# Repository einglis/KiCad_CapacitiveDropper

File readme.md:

# Gate Light Capacitive Dropper

I bought some LED tape (https://www.amazon.co.uk/dp/B07KW4Q4R3) to make lights for my gateposts.

In stock trim, they're too bright, and they flicker in my peripheral vision, which is very annoying.

BigClive has a nice article about hacking LED bulbs here: https://bigclive.com/ledlmp.htm.  It applies equally well to these LED tapes.

Because I'm indecisive, I made three variants...

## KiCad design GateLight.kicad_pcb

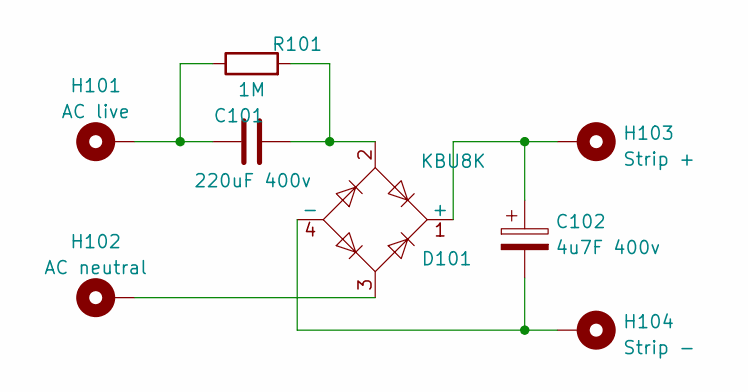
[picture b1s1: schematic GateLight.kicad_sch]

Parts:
C101: 220uF 400v; C_Rect_L16.5mm_W9.2mm_P15.00mm_MKT
C102: 4u7F 400v; CP_Radial_L13.0mm_D10.0mm_P5.00mm_Horizontal
D101: KBU8K; Diode_Bridge_Vishay_KBU
H101: AC live; MountingHole_2.2mm_M2_Pad
H102: AC neutral; MountingHole_2.2mm_M2_Pad
H103: Strip +; MountingHole_2.2mm_M2_Pad
H104: Strip -; MountingHole_2.2mm_M2_Pad
R101: 1M; R_Axial_DIN0207_L6.3mm_D2.5mm_P7.62mm_Horizontal

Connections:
unnamed: C101.1, D101.2, R101.2
unnamed: C101.2, H101.1, R101.1
unnamed: C102.1, D101.1 (+), H103.1
unnamed: C102.2, D101.4 (-), H104.1
unnamed: D101.3, H102.1

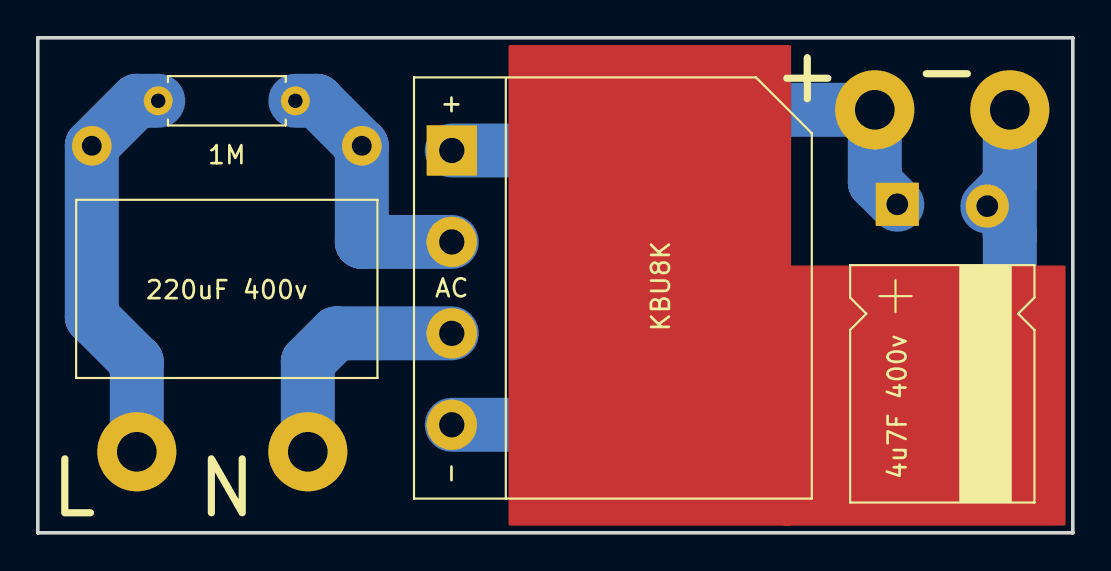
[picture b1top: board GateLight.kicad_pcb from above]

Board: 2 copper layers, 57.5 x 27.5 mm, 8 parts (0 on the bottom side), 5 nets.

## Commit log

2023-12-17 initial version
2023-12-17 first pass at fabrication; two designs
2023-12-17 a third version!
2023-12-17 docs
